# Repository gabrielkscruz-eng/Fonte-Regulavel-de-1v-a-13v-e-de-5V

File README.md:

# Fonte de Alimentação de Bancada

Projeto de desenvolvimento de **fontes de alimentação para bancada**, realizado no curso de **Engenharia da Computação da Universidade Santa Cecília (UNISANTA)**.

O repositório reúne duas etapas do desenvolvimento:

* **Fonte de alimentação fixa de 5 V**
* **Fonte de alimentação regulável bivolt**

O projeto envolveu o desenvolvimento dos circuitos eletrônicos, criação das placas de circuito impresso, prototipagem, testes e desenvolvimento do encapsulamento da fonte regulável.

---

## Sobre o projeto

Fontes de alimentação são utilizadas para fornecer tensão adequada e estável para circuitos eletrônicos. Em aplicações de bancada, uma fonte regulável permite trabalhar com diferentes níveis de tensão durante testes e desenvolvimento de circuitos.

Neste projeto foram desenvolvidas duas fontes em etapas. A primeira foi uma **fonte fixa de 5 V**, utilizada como uma etapa inicial de desenvolvimento. Posteriormente, foi desenvolvida uma **fonte regulável bivolt**, incorporando uma saída fixa de 5 V e uma saída variável.

O desenvolvimento permitiu aplicar conhecimentos relacionados a **retificação, filtragem, regulagem de tensão, dissipação térmica, proteção de componentes, desenvolvimento de PCB e fabricação do encapsulamento**.

---

# Fonte de 5 V

A primeira etapa do projeto consistiu no desenvolvimento de uma fonte com **saída fixa de 5 V**.

O circuito utiliza o **LM7805** como regulador de tensão e foi desenvolvido utilizando o KiCad.

### Principais características

* Saída regulada de **5 V DC**
* Regulador **LM7805**
* Circuito de retificação
* Filtragem da tensão
* Capacitores para estabilização
* PCB própria

### Fluxo simplificado

```text
Entrada AC
    │
    ▼
Transformação
    │
    ▼
Retificação
    │
    ▼
Filtragem
    │
    ▼
LM7805
    │
    ▼
Saída 5 V DC
```

Os arquivos referentes à fonte fixa estão disponíveis na pasta:

**[`Fonte_5V_Fixa`](./Fonte_5V_Fixa/)**

Nela estão disponíveis os arquivos de projeto do KiCad e os documentos em PDF referentes ao esquemático e à placa.

---

# Fonte Regulável Bivolt

A segunda etapa consistiu no desenvolvimento de uma **fonte de alimentação regulável e bivolt**.

O projeto foi desenvolvido com o objetivo de possuir uma entrada selecionável entre **110 V e 220 V**, uma saída fixa de 5 V e uma saída variável.

O projeto também incluiu o desenvolvimento da PCB, sistema de ventilação e encapsulamento físico.

## Especificações finais

| Característica              | Especificação      |
| --------------------------- | ------------------ |
| Entrada                     | 110/220 V AC       |
| Transformador               | 12 V / 3 A         |
| Saída fixa                  | 5 V DC             |
| Saída variável              | **11 V a 13 V DC** |
| Regulador da saída variável | LM317              |
| Regulador da saída de 5 V   | LM7805             |
| Regulador de 12 V           | LM7812             |
| Ponte retificadora          | KBU808             |
| Potenciômetro               | 10 kΩ              |
| Dimensão da PCB             | 10 × 7,5 cm        |
| Dimensão do gabinete        | 15 × 11 × 15 cm    |
| Material do gabinete        | MDF                |

A relação de componentes do projeto inclui, entre outros, ponte retificadora KBU808, reguladores LM7805, LM7812 e LM317, diodos 1N4004, capacitores de 4700 µF, capacitores de desacoplamento, resistor de 220 Ω e potenciômetro de 10 kΩ.

---

# Funcionamento

O funcionamento da fonte regulável pode ser dividido em algumas etapas principais:

```text
                 ┌──────────────► LM7805 ───► 5 V DC
                 │
Rede AC          │
  │              │
  ▼              │
Seletor          │
110/220 V        │
  │              │
  ▼              │
Transformador    │
12 V / 3 A       │
  │              │
  ▼              │
KBU808            │
Retificação       │
  │              │
  ▼              │
Filtragem         │
4700 µF           │
  │              │
  ├───────────────┼──────► LM7812 ───► 12 V
  │              │
  │              └──────► LM317 ────► Saída variável
  │                                      │
  ▼                                      ▼
Tensão DC filtrada                    11 V ~ 13 V
```

O transformador reduz a tensão da rede, a ponte KBU808 realiza a retificação e os capacitores fazem a filtragem da tensão. Após essa etapa, os reguladores são responsáveis por gerar as saídas previstas no projeto.

---

# Componentes principais

## Fonte regulável

* Transformador bivolt **12 V / 3 A**
* Ponte retificadora **KBU808**
* **LM7805**
* **LM7812**
* **LM317**
* 3 × diodos **1N4004**
* 2 × capacitores eletrolíticos **4700 µF**
* 2 × capacitores **0,33 µF**
* 3 × capacitores **0,1 µF**
* Resistor **220 Ω**
* Potenciômetro **10 kΩ**
* 6 × conectores borne
* Seletor **110/220 V**
* Chave alavanca
* Fusível
* Conector para cabo de alimentação

---

# Desenvolvimento da PCB

A esquemática e o layout da placa foram desenvolvidos utilizando o **KiCad 7.0**.

A PCB possui dimensões de aproximadamente:

**10 × 7,5 cm**

A fabricação da placa foi realizada por meio de **fresagem em placa de fenolite** nas instalações do **INOVFabLab da Universidade Santa Cecília**.

Os arquivos editáveis do KiCad estão disponíveis diretamente neste repositório, permitindo visualizar e modificar o projeto eletrônico.

### Arquivos disponíveis

```text
Fonte_regulavel/
├── fonte_regulavel.kicad_pro
├── fonte_regulavel.kicad_sch
├── fonte_regulavel.kicad_pcb
├── Esquemática Fonte regulavel.pdf
└── Placa da Fonte Regulavel.pdf
```

---

# Desenvolvimento do encapsulamento

O encapsulamento da fonte regulável foi desenvolvido utilizando o **Autodesk Fusion 360**.

A estrutura foi projetada para acomodar a placa eletrônica e os demais componentes da fonte.

A fabricação foi realizada em **MDF utilizando corte a laser**.

### Dimensões

**15 × 11 × 15 cm**

Foi utilizada uma placa de MDF de 1,3 × 0,9 m para a fabricação do gabinete.

O arquivo do encapsulamento está disponível na pasta:

**[`Gabinete`](./Gabinete/)**

---

# Evolução do projeto

O desenvolvimento da fonte regulável ocorreu a partir da experiência obtida durante a primeira etapa do projeto.

Inicialmente, foi planejada a utilização de duas placas. A placa da entrega parcial possuía saídas fixas de **5 V e 12 V**, sendo a saída de 5 V destinada à carga e a saída de 12 V destinada à ventoinha utilizada para auxiliar no resfriamento do regulador.

Durante a prototipagem foram identificados problemas na placa da entrega parcial. Como consequência, foi decidido integrar os componentes em uma única placa.

Também houve uma alteração no circuito da saída variável. O circuito inicialmente planejado foi substituído pelo **LM317**, devido à praticidade de implementação.

---

# Resultado final

Após a montagem e os testes do protótipo, foram obtidas as seguintes saídas:

### Saída fixa

**5 V DC**

### Saída variável

**11 V a 13 V DC**

A saída variável apresentada neste README corresponde ao **resultado final obtido nos testes do protótipo**.

O relatório acadêmico registra, em sua seção de resultados, uma faixa de 1,10 V a 13 V para o protótipo documentado naquele momento. O valor de **11 V a 13 V** apresentado aqui corresponde ao resultado final considerado para este repositório.

---

# Comparação das duas fontes

| Característica |        Fonte 5 V | Fonte Regulável |
| -------------- | ---------------: | --------------: |
| Saída fixa     |              5 V |             5 V |
| Saída variável |              Não |         11–13 V |
| Entrada bivolt | Não especificada |       110/220 V |
| LM7805         |              Sim |             Sim |
| LM7812         |              Não |             Sim |
| LM317          |              Não |             Sim |
| PCB            |              Sim |             Sim |
| Encapsulamento |              Não |             MDF |
| Ventilação     |              Não |             Sim |

---

# Organização do repositório

```text
Fonte-Regulavel-de-1v-a-13v-e-de-5V-main/
│
├── README.md
│
├── Documentação/
│   └── RELATÓRIO FONTE.pdf
│
├── Fonte_5V_Fixa/
│   ├── Esquemática da placa de 5V.pdf
│   ├── Fonte_5v.kicad_pcb
│   ├── Fonte_5v.kicad_pro
│   ├── Fonte_5v.kicad_sch
│   └── Placa de 5V.pdf
│
├── Fonte_regulavel/
│   ├── Esquemática Fonte regulavel.pdf
│   ├── Placa da Fonte Regulavel.pdf
│   ├── fonte_regulavel.kicad_pcb
│   ├── fonte_regulavel.kicad_pro
│   └── fonte_regulavel.kicad_sch
│
└── Gabinete/
    └── Encapsulamento da Fonte regulavel.rld
```

---

# Documentação

O relatório técnico completo do projeto está disponível em formato PDF na pasta **Documentação**.

📄 **[Relatório Técnico](./Documentação/RELATÓRIO%20FONTE.pdf)**

O relatório apresenta:

* Introdução e objetivos;
* Materiais e métodos;
* Desenvolvimento do circuito;
* Desenvolvimento das placas;
* Desenvolvimento do encapsulamento;
* Resultados;
* Conclusão;
* Referências;
* Imagens e registros do projeto.

As **imagens e registros visuais do desenvolvimento e da fonte final estão disponíveis no relatório técnico em PDF**.

Além do relatório, os PDFs de esquemática e layout das placas estão disponíveis nas respectivas pastas dos projetos.

---

# Ferramentas utilizadas

### Projeto eletrônico

* **KiCad 7.0**
* Desenvolvimento de esquemática
* Desenvolvimento de PCB
* Geração dos arquivos de fabricação

### Projeto mecânico

* **Autodesk Fusion 360**
* Modelagem do encapsulamento

### Fabricação

* Fresagem de PCB em placa de fenolite
* Corte a laser de MDF

---

# Objetivos acadêmicos

O projeto teve como objetivo aplicar, de forma prática, conhecimentos adquiridos na disciplina de **Tópicos de Eletrônica**, abrangendo diferentes etapas do desenvolvimento de hardware.

Entre os principais conhecimentos aplicados estão:

* Retificação de tensão;
* Filtragem;
* Regulagem de tensão;
* Utilização de reguladores lineares;
* Dissipação térmica;
* Proteção de componentes;
* Desenvolvimento de PCB;
* Montagem eletrônica;
* Projeto mecânico;
* Fabricação digital;
* Testes e validação de hardware.

O desenvolvimento permitiu compreender na prática as etapas necessárias para transformar um circuito eletrônico em um equipamento físico funcional.

---

# Autores

**Caique Caruso Toscani da Costa**

**Gabriel Kevin Souza Cruz**

**Curso de Engenharia da Computação**
**Universidade Santa Cecília — UNISANTA**

Santos, São Paulo — Brasil
2026

---

# Segurança

> **ATENÇÃO:** este projeto trabalha com tensão de rede elétrica de **110/220 V AC**.

A montagem, manutenção ou reprodução do circuito deve ser realizada com procedimentos adequados de segurança elétrica e por pessoas capacitadas.

Este projeto foi desenvolvido para fins **acadêmicos e educacionais**.

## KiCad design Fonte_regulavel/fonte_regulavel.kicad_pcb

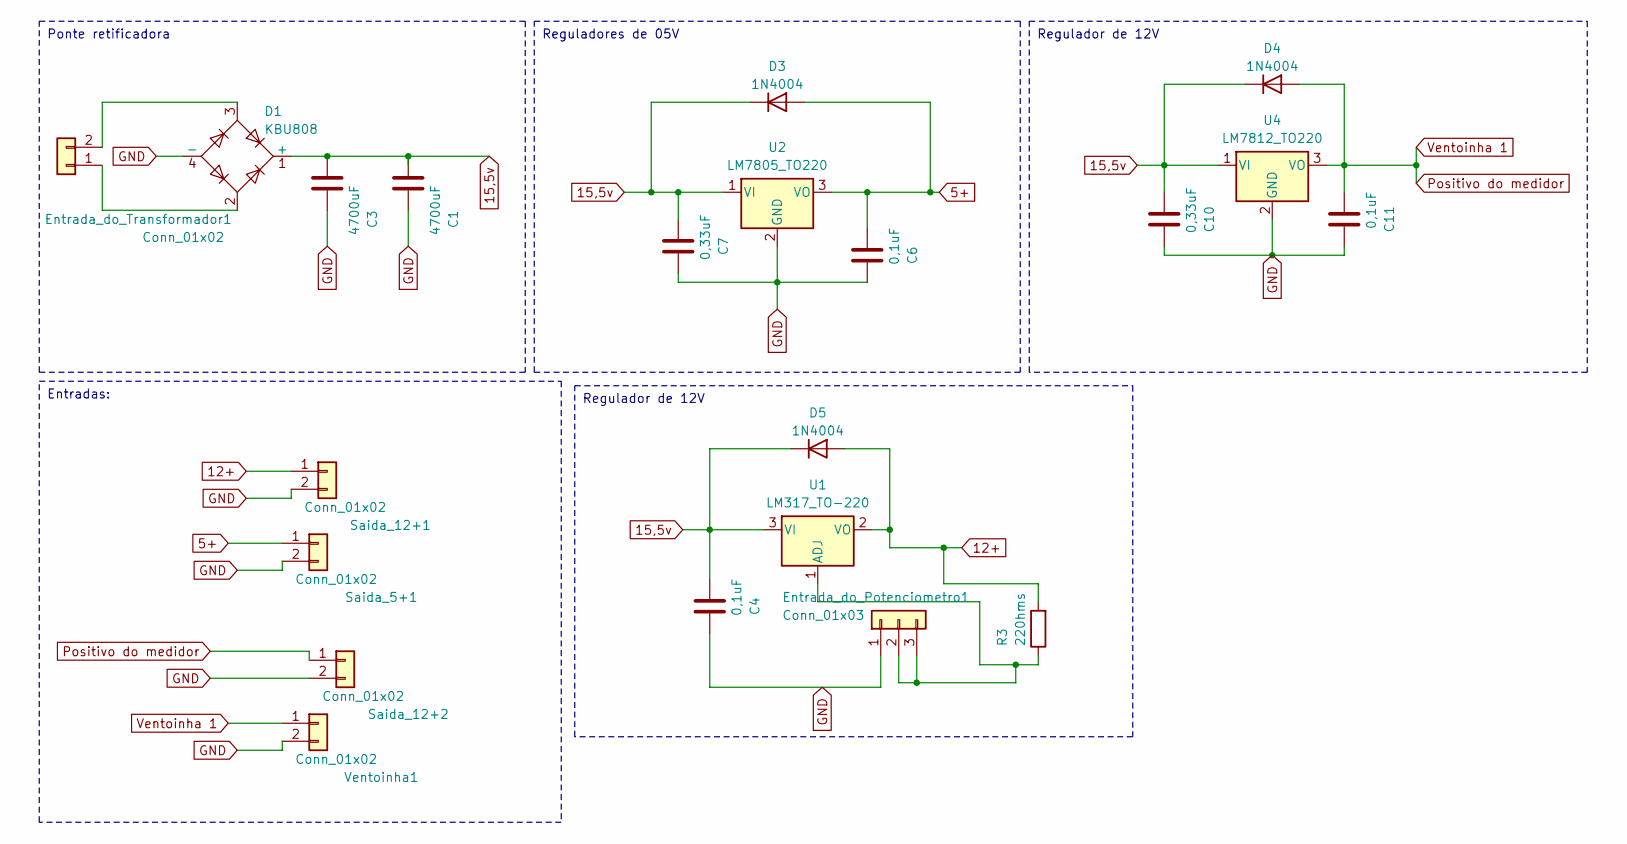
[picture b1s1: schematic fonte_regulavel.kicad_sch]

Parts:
C1, C3: 4700uF; CP_Radial_D18.0mm_P7.50mm
C4, C6, C11: 0,1uF; C_Disc_D3.8mm_W2.6mm_P2.50mm
C7, C10: 0,33uF; C_Disc_D3.8mm_W2.6mm_P2.50mm
D1: KBU808; Diode_Bridge_Vishay_KBU
D3, D4, D5: 1N4004; D_DO-41_SOD81_P10.16mm_Horizontal
Entrada_do_Potenciometro1: Conn_01x03; TerminalBlock_bornier-3_P5.08mm
Entrada_do_Transformador1: Conn_01x02; TerminalBlock_bornier-2_P5.08mm
R3: 220hms; R_Axial_DIN0207_L6.3mm_D2.5mm_P10.16mm_Horizontal
Saida_5+1, Saida_12+1, Saida_12+2: Conn_01x02; TerminalBlock_bornier-2_P5.08mm
U1: LM317_TO-220; TO-220-3_Vertical
U2: LM7805_TO220; TO-220-3_Vertical
U4: LM7812_TO220; TO-220-3_Vertical
Ventoinha1: Conn_01x02; TerminalBlock_bornier-2_P5.08mm

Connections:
5+: C6.1, D3.2 (A), Saida_5+1.1, U2.3 (VO)
12+: D5.2 (A), R3.2, Saida_12+1.1, U1.2 (VO)
15,5v: C1.1, C3.1, C4.1, C7.1, C10.1, D1.1 (+), D3.1 (K), D4.1 (K), D5.1 (K), U1.3 (VI), U2.1 (VI), U4.1 (VI)
GND: C1.2, C3.2, C4.2, C6.2, C7.2, C10.2, C11.2, D1.4 (-), Entrada_do_Potenciometro1.1, Saida_5+1.2, Saida_12+1.2, Saida_12+2.2, U2.2 (GND), U4.2 (GND), Ventoinha1.2
unnamed: Entrada_do_Potenciometro1.2, Entrada_do_Potenciometro1.3, R3.1, U1.1 (ADJ)
unnamed: D1.2, Entrada_do_Transformador1.1
unnamed: D1.3, Entrada_do_Transformador1.2
Positivo do medidor: C11.1, D4.2 (A), Saida_12+2.1, U4.3 (VO), Ventoinha1.1

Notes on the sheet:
Regulador de 12V
Reguladores de 05V
Entradas:
Ponte retificadora

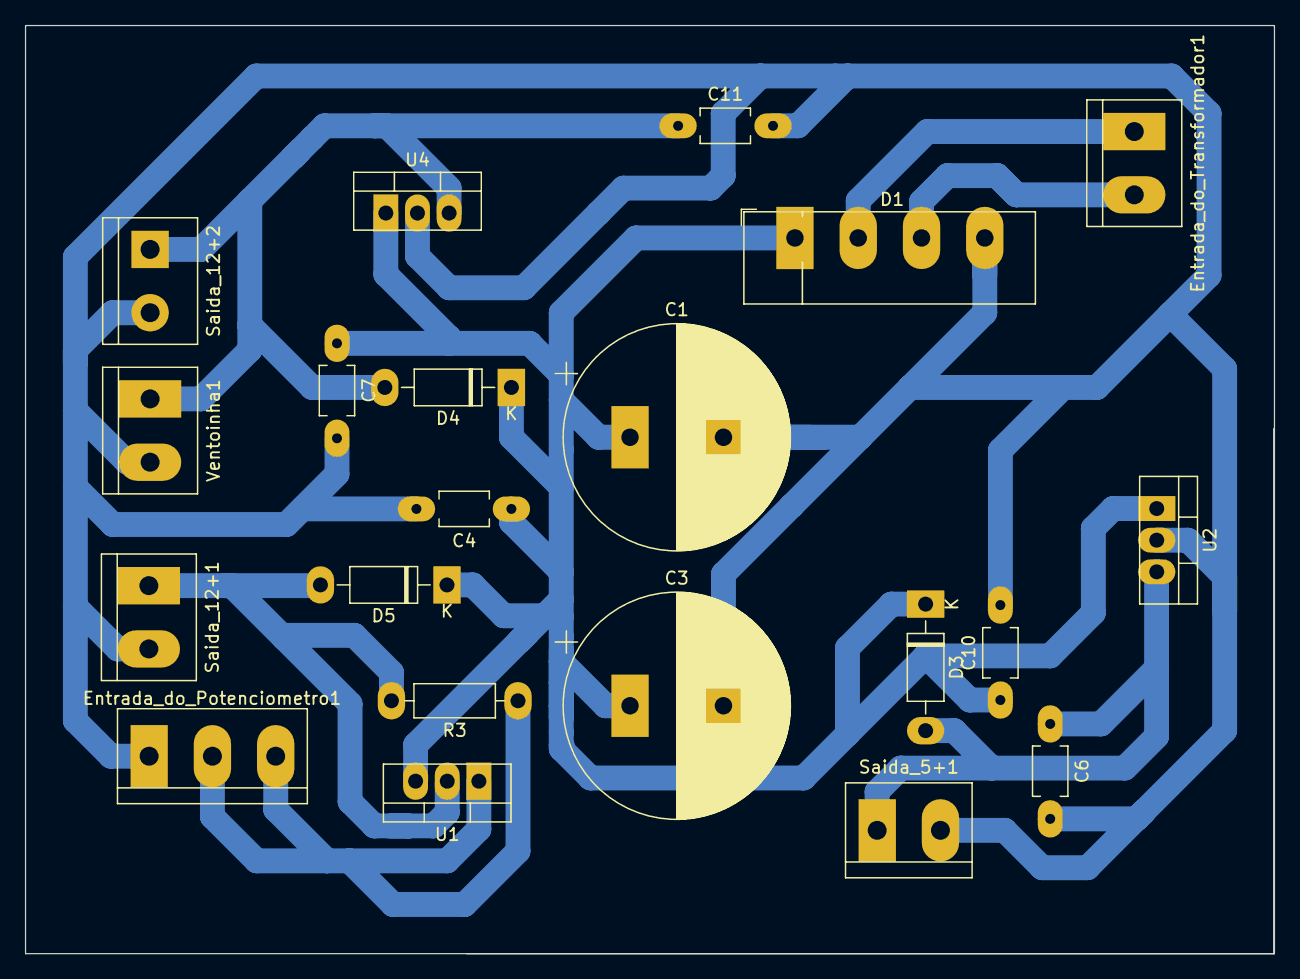
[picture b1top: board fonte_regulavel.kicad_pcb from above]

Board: 2 copper layers, 100.2 x 74.5 mm, 21 parts (0 on the bottom side), 8 nets.

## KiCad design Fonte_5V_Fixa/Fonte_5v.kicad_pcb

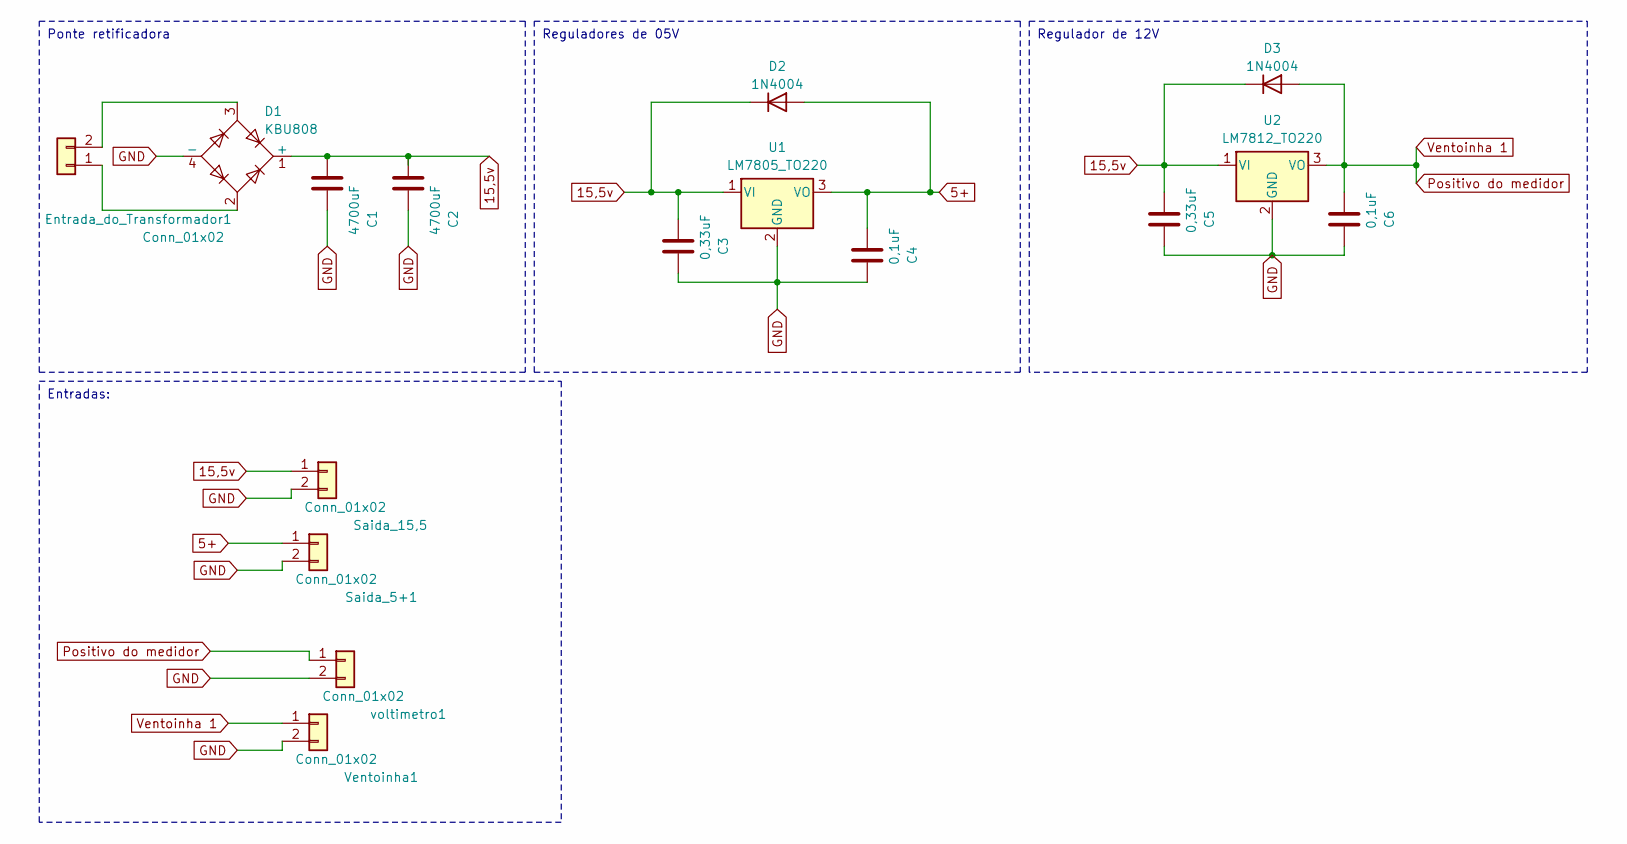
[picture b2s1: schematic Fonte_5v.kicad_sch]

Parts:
C1, C2: 4700uF; CP_Radial_D18.0mm_P7.50mm
C3, C5: 0,33uF; C_Disc_D3.8mm_W2.6mm_P2.50mm
C4, C6: 0,1uF; C_Disc_D3.8mm_W2.6mm_P2.50mm
D1: KBU808; Diode_Bridge_Vishay_KBU
D2, D3: 1N4004; D_DO-41_SOD81_P10.16mm_Horizontal
Entrada_do_Transformador1: Conn_01x02; TerminalBlock_bornier-2_P5.08mm
Saida_5+1, Saida_15,5: Conn_01x02; TerminalBlock_bornier-2_P5.08mm
U1: LM7805_TO220; TO-220-3_Vertical
U2: LM7812_TO220; TO-220-3_Vertical
Ventoinha1: Conn_01x02; TerminalBlock_bornier-2_P5.08mm
voltimetro1: Conn_01x02; TerminalBlock_bornier-2_P5.08mm

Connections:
5+: C4.1, D2.2 (A), Saida_5+1.1, U1.3 (VO)
15,5v: C1.1, C2.1, C3.1, C5.1, D1.1 (+), D2.1 (K), D3.1 (K), Saida_15,5.1, U1.1 (VI), U2.1 (VI)
GND: C1.2, C2.2, C3.2, C4.2, C5.2, C6.2, D1.4 (-), Saida_5+1.2, Saida_15,5.2, U1.2 (GND), U2.2 (GND), Ventoinha1.2, voltimetro1.2
unnamed: D1.2, Entrada_do_Transformador1.1
unnamed: D1.3, Entrada_do_Transformador1.2
Positivo do medidor: C6.1, D3.2 (A), U2.3 (VO), Ventoinha1.1, voltimetro1.1

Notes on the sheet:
Entradas:
Reguladores de 05V
Regulador de 12V
Ponte retificadora

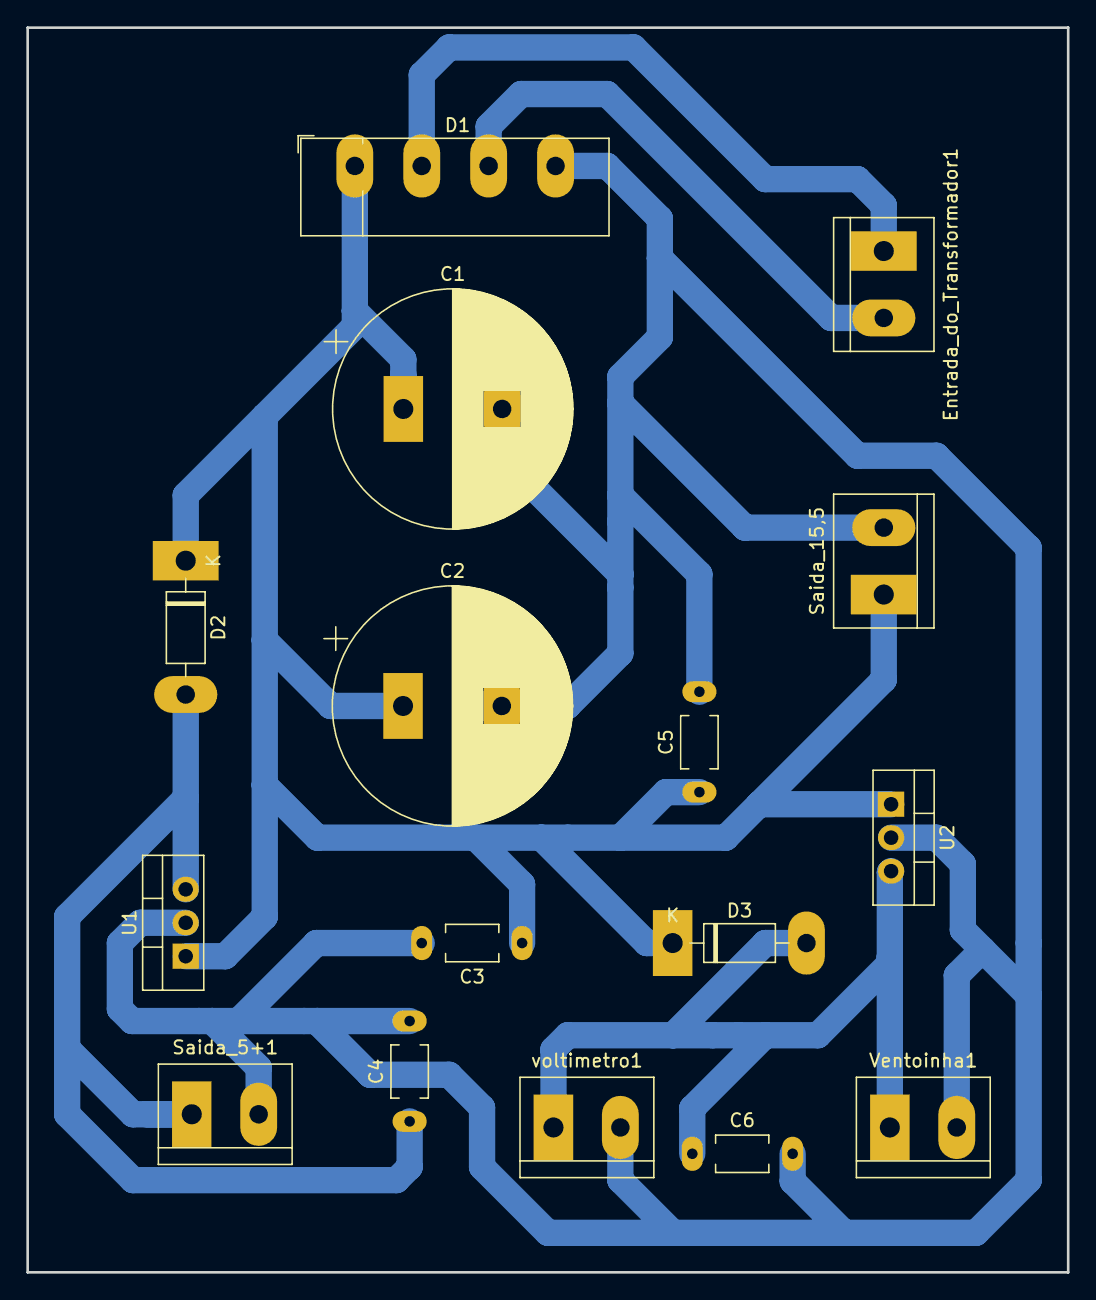
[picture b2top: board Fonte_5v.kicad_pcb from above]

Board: 2 copper layers, 79.0 x 94.5 mm, 16 parts (0 on the bottom side), 6 nets.
